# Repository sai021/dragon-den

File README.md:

# Dragon Den

A touch-controlled dragon lightbox with a phone interface for children and
their parents. An ESP32-S3 drives an 8×8 RGB LED matrix behind a dragon face.
Families can pick dragons, play lighting effects, save personal collections,
and make custom dragons without installing an app or writing code.

**Current state: working development prototype, documented 15 October 2026.**
The firmware is installed on the wired prototype. Phone workflows have been
tested with simulated responses, and hardware startup has been observed. PCB
manufacturing, optical fit, the complete physical-phone test matrix, and the
deployed external power supply have outstanding checks.

## What works

- Tap for the next dragon, double tap for sleep/wake, hold for brightness.
- 81 supplied dragon palettes, plus eight saved custom creations.
- Four profiles: protected **All** and three named collections.
- Named profiles show favourites plus their own creations; physical taps use
  the same collection. Empty profiles invite you to add or create dragons.
- Profile deletion preserves its creations by moving them into All.
- A phone editor for ten regions, including separate wing edges and interiors.
  Untouched regions retain imported pixel variations. Save, copy and delete
  creations, with rainbow, breathing, shimmer and glitter by region.
- One-button glitter, fire, breathing and rainbow, glow control and sleep/wake.
- On-device Wi-Fi setup, nearby network search and saved home-network details.
  Everyday play does not require internet or an account.
- Automatic ambient dimming and startup selection of an estimated power ceiling.

Weather animations, a parent PIN, firmware updates through the web interface,
and export/import backups are not implemented yet.

## Start here

| Reader | Guide |
| --- | --- |
| Parents testing a prepared device | [Phone and touch guide](docs/PARENT-GUIDE.md) |
| End users and families | [Printable user manual](output/pdf/dragon-den-user-manual.pdf) / [editable text](docs/USER-MANUAL.md) |
| Developers setting up another computer | [Build and test](docs/DEVELOPMENT.md) |
| Hardware assembly and power | [Hardware wiring](dragon-firmware/HARDWARE-WIRING.md) |
| Profiles and custom dragons | [Collections and editing](dragon-firmware/PROFILES-AND-CREATIONS.md) |
| Wi-Fi setup and recovery | [Web setup](dragon-firmware/WEB-SETUP.md) |
| Current evidence and unfinished checks | [Project status](docs/PROJECT-STATUS.md) |
| System design and API | [Architecture](docs/ARCHITECTURE.md) |
| Optical/CAD prototype | [Mechanical assets](docs/MECHANICAL-ASSETS.md) |

## Power arrangement

During development, laptop USB-C powers the connected circuit through the
ESP32 USB connector. **External/main power must remain disconnected.** When a
computer USB host is detected, firmware retains a 400 mA **estimated** session
ceiling. This is a model-based limit, not USB power negotiation or a current
measurement.

In the deployed product, the external product supply powers the matrix
directly through the shared 5 V rail. The ESP32 board/USB connector is not the
intended matrix power source. Disconnect laptop USB before external-only tests.
Never connect both powered inputs simultaneously with the current circuit.

## Repository map

```text
docs/                         consolidated project and parent guides
dragon-firmware/
  DragonPrototype/            Arduino sketch, renderer, storage, web API
  web/                        editable offline phone page and editor
  presets/                    editable supplied dragon catalog
  tools/                      build, import, desktop editor and test helpers
  tests/                      native C++, Python and browser checks
  hardware/                   CAD sources, exports and dated Gerber reviews
dragon-masks/                 registered optical masks and artwork references
  light-guide/                canonical mesh build/check scripts and reports
dragon-light-guide-prototype/ legacy delivery notes and validation reports
```

Local runtimes, firmware binaries, logs, device credentials, printable setup
cards, generated large STL meshes, and duplicate ZIP bundles are excluded
from Git. See [mechanical assets](docs/MECHANICAL-ASSETS.md) to rebuild the mesh.
Nothing is deleted from the local workspace by these exclusions.

## Reproduce the firmware

Install Python 3 and Arduino CLI, then run from `dragon-firmware`:

```sh
python tools/dev.py setup
python tools/dev.py build
python tools/dev.py ports
python tools/dev.py upload --port YOUR_PORT
```

Use the actual detected port, not a port copied from a test log. Close serial
monitors before uploading. Build uses Arduino-ESP32 3.2.1, Adafruit NeoPixel
1.12.5, 4 MB flash, 2 MB PSRAM and the supplied custom partitions.

The build regenerates palette and embedded-page headers. Keep
`DragonPrototype/build_opt.h`: its network-event locking fixed a reproduced
startup crash in this pinned core. Full instructions and tests are in
[DEVELOPMENT.md](docs/DEVELOPMENT.md).

## Provenance

See [asset and dependency notes](docs/PROVENANCE.md). No blanket licence is
being applied to supplied character palettes, artwork, or third-party CAD
symbols. Their existing notices and provenance are retained.

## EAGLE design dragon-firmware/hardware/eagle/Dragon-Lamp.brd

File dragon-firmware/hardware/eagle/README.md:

# Dragon lamp PCB interface schematic

J1 is an eight-pin 2.54 mm female socket for the ESP32 row, following the supplied order. The square pad is pin 1 (5V). Check socket orientation against the board before soldering.

| Connector | Pin order |
| --- | --- |
| J1 ESP32 socket | 1=5V, 2=GND, 3=3V3, 4=GPIO13 (unused), 5=GPIO12 matrix, 6=GPIO11 touch, 7=GPIO10 voltage, 8=GPIO9 LDR |
| J2 remote matrix | 1=5V, 2=GND, 3=DIN |
| J3 remote TTP223 | 1=3V3, 2=GND, 3=OUT |
| J4 remote USB-C power board | 1=VBUS/5V, 2=GND |
| J5 remote LDR | 1=3V3, 2=GPIO9 |

The LDR, touch sensor, LED matrix, USB-C board and electrolytic capacitor are off the PCB. The 1000uF electrolytic is installed across VBUS/GND at the USB-C board, with correct polarity; no PCB footprint is reserved for it. Its supplied dimensions are 8 mm diameter and 16.5 mm height.

R1=330R LED data series resistor. R3=10k LDR pulldown. R4=100k and R5=20k form the supply divider. All four use upright resistor footprints with 2.54 mm lead spacing and an assumed 2.5 mm body diameter. This is lead spacing, not total occupied width; allow body and bent-lead clearance in layout.

C2=100nF PCB touch-supply bypass. Keep a 100nF bypass near the remote TTP223 supply pins as well. C3=optional 100nF LDR filter. C4=100nF voltage-divider filter. Ceramic footprints use 5.00 mm lead spacing and an assumed 5 x 2.5 mm body envelope. Check the actual capacitor bodies before placement.

EAGLE packages are embedded with explicit pin-to-pad mappings. All module interfaces use 2.54 mm through-hole connectors; J1 accepts a matching single-row female socket. Header holes are 1.0 mm, discrete holes 0.9 mm, pad diameters 1.8 mm. J2-J5 pin order defines the wiring harness, not the physical module pin order.

Validation: 12 parts, 32 physical pins/pads, 31 connected pins and one intentionally unused GPIO13 pad; eight nets checked for continuity and unintended endpoint contacts. All EAGLE pin coordinates and net memberships match the KiCad source. Native application import/ERC/DRC has not been run. Preview.svg is generated from the source symbol geometry, not a native CAD screenshot. This is a schematic with packages, not a routed or fabrication-ready PCB. KiCad source symbols remain without footprint assignments; packages are assigned in the EAGLE export.

Use PC USB OR external 5V unless powered sources are isolated. All grounds are common. The USB-C breakout retains its existing CC resistors. Direct 3.3V LED data follows the prototype; logic-level requirements depend on the matrix variant.

Symbol geometry is from official KiCad 8 libraries; see LICENSE.txt.

Import compatibility revision: import hardware/Dragon-Lamp-EasyEDA-Import.zip as an EAGLE project. It contains matching Dragon-Lamp.sch and Dragon-Lamp.brd; the board includes all physical packages and identical signal assignments. Device variants now have explicit -THT names and proper R/C/J prefixes. Dragon-Parts.lbr is also supplied separately in the full archive. The PCB is an unrouted, spaced collection of components without a board outline, not a finished layout. This revision is a compatibility workaround; EasyEDA import is not yet verified. The J1.4 X in EAGLE is graphical only: in EasyEDA place a native No Connect flag on J1.4 (unused GPIO13). Do not connect that pad to ground. If missing-footprint errors persist, export the imported EasyEDA project so its internal IDs and footprint bindings can be inspected.

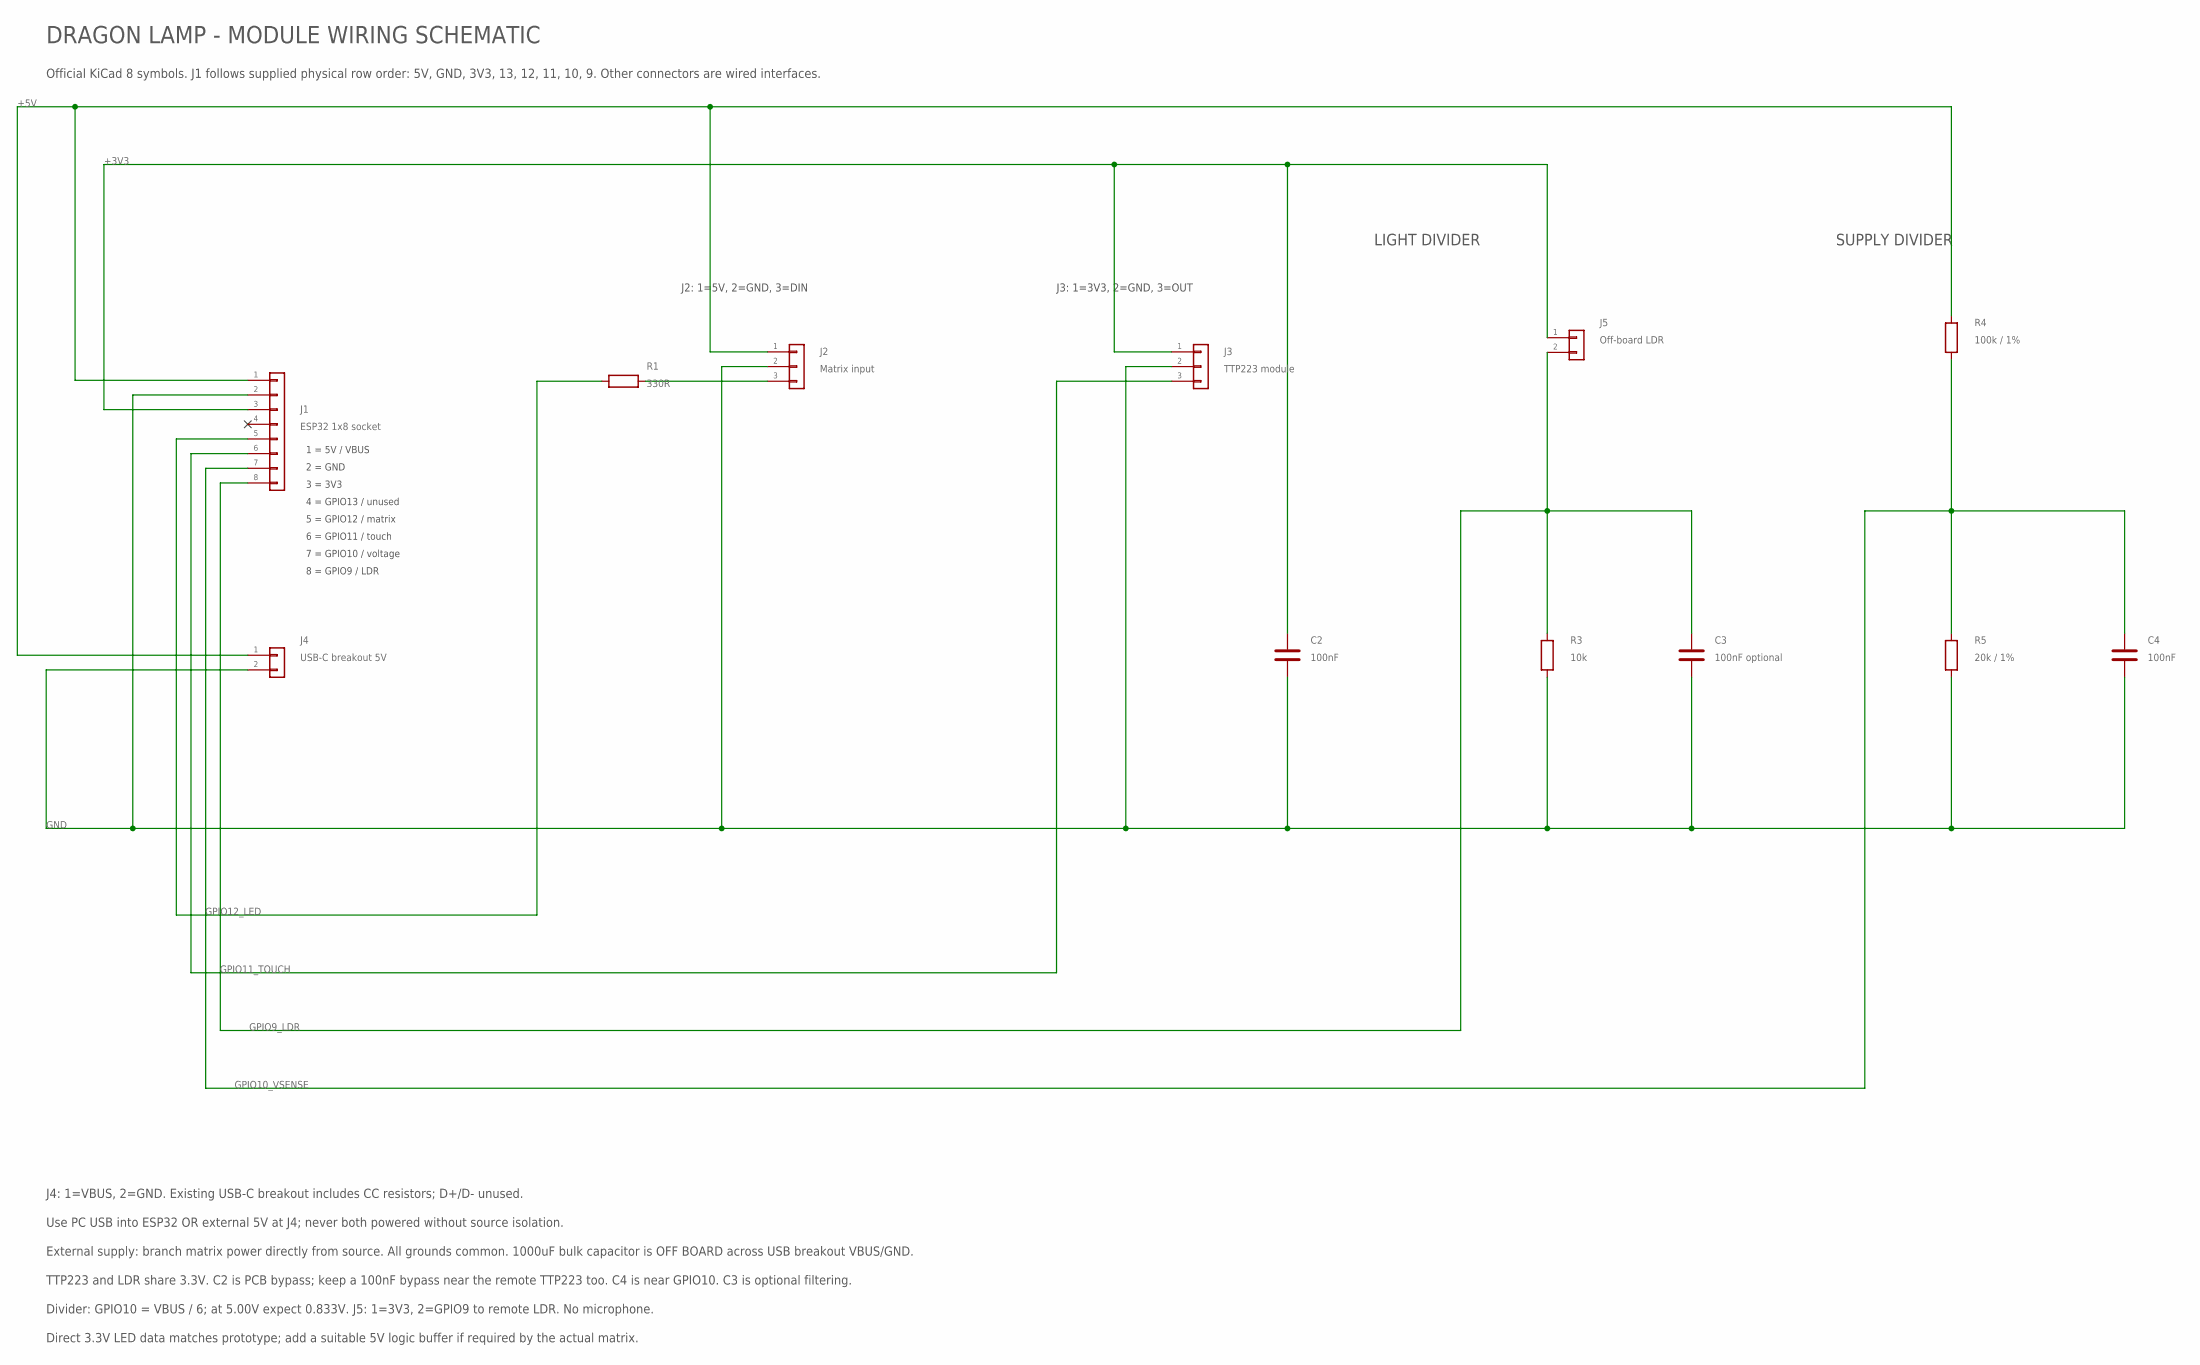
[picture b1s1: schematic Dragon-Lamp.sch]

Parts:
C2, C4: 100nF; C_DISC_P5.00
C3: 100nF optional; C_DISC_P5.00
J1: ESP32 1x8 socket; HEADER_1X8_P2.54
J2: Matrix input; HEADER_1X3_P2.54
J3: TTP223 module; HEADER_1X3_P2.54
J4: USB-C breakout 5V; HEADER_1X2_P2.54
J5: Off-board LDR; HEADER_1X2_P2.54
R1: 330R; R_VERTICAL_P2.54
R3: 10k; R_VERTICAL_P2.54
R4: 100k / 1%; R_VERTICAL_P2.54
R5: 20k / 1%; R_VERTICAL_P2.54

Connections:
+3V3: C2.1, J1.3, J3.1, J5.1
+5V: J1.1, J2.1, J4.1, R4.1
GND: C2.2, C3.2, C4.2, J1.2, J2.2, J3.2, J4.2, R3.2, R5.2
GPIO9_LDR: C3.1, J1.8, J5.2, R3.1
GPIO10_VSENSE: C4.1, J1.7, R4.2, R5.1
GPIO11_TOUCH: J1.6, J3.3
GPIO12_LED: J1.5, R1.2
LED_DIN: J2.3, R1.1

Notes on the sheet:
1 = 5V / VBUS
2 = GND
3 = 3V3
4 = GPIO13 / unused
5 = GPIO12 / matrix
6 = GPIO11 / touch
7 = GPIO10 / voltage
8 = GPIO9 / LDR
DRAGON LAMP - MODULE WIRING SCHEMATIC
Official KiCad 8 symbols. J1 follows supplied physical row order: 5V, GND, 3V3, 13, 12, 11, 10, 9. Other connectors are wired interfaces.
J2: 1=5V, 2=GND, 3=DIN
J3: 1=3V3, 2=GND, 3=OUT
LIGHT DIVIDER
SUPPLY DIVIDER
J4: 1=VBUS, 2=GND. Existing USB-C breakout includes CC resistors; D+/D- unused.
Use PC USB into ESP32 OR external 5V at J4; never both powered without source isolation.
External supply: branch matrix power directly from source. All grounds common. 1000uF bulk capacitor is OFF BOARD across USB breakout VBUS/GND.
TTP223 and LDR share 3.3V. C2 is PCB bypass; keep a 100nF bypass near the remote TTP223 too. C4 is near GPIO10. C3 is optional filtering.
Divider: GPIO10 = VBUS / 6; at 5.00V expect 0.833V. J5: 1=3V3, 2=GPIO9 to remote LDR. No microphone.
Direct 3.3V LED data matches prototype; add a suitable 5V logic buffer if required by the actual matrix.

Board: 1 copper layer, 12 parts (0 on the bottom side), 8 nets, no tracks yet.

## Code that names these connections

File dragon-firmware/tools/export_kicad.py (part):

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 label(xs[0],y,net)
# Matrix data: real series resistor between GPIO12 and DIN.
route('LED_DIN',p('R1',1),p('J2',3));expected['R1','1']=expected['J2','3']='LED_DIN'
for num,net,target,tx,ry in [(5,'GPIO12_LED',p('R1',2),100,165),(6,'GPIO11_TOUCH',p('J3',3),190,175),(8,'GPIO9_LDR',(260,95),260,185),(7,'GPIO10_VSENSE',(330,95),330,195)]:
 a=p('J1',num);lx=35+(num-4)*2.54
 route(net,a,(lx,a[1]),(lx,ry),(tx,ry),(tx,target[1]),target)
 label(lx+5,ry,net);expected['J1',str(num)]=net
expected['R1','2']='GPIO12_LED';expected['J3','3']='GPIO11_TOUCH'
for net,upper,lower,cap,x,cx,tx in [('GPIO9_LDR','J5','R3','C3',275,300,260),('GPIO10_VSENSE','R4','R5','C4',345,375,330)]:
 route(net,p(upper,2),(x,95),p(lower,1))
 route(net,(tx,95),(x,95),(cx,95),p(cap,1));dot(x,95)
 expected[upper,'2']=expected[lower,'1']=expected[cap,'1']=net
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

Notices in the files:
parts and their libraries:
Dragon_KiCad_Official: Converted official KiCad 8.0.0 symbols; see included license. Module connectors are logical wiring terminals.
